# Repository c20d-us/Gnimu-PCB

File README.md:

<p>
  
  <picture>
    <source media="(prefers-color-scheme: dark)" srcset="https://raw.githubusercontent.com/c20d-us/Gnimu-branding/main/wordmark/gnimu-wordmark-transparent-white.svg">
    
  </picture>
</p>

# Gnimu PCBs

Circuit boards for [Gnimu](https://github.com/c20d-us/Gnimu), a GNSS+IMU motorsports telemetry device that streams live position, speed, and motion data over BLE.

This repository holds the hardware only: KiCad projects, the shared symbol and footprint library, and fabrication outputs. The firmware, the bill of materials, and the step-by-step build guides live in the [Gnimu](https://github.com/c20d-us/Gnimu) repository.

<table>
  <tr>
    <td align="center" valign="top" width="50%">
      <br>
      <sub>The bare carrier (revision v1.0), front and back.</sub>
    </td>
    <td align="center" valign="top" width="50%">
      <br>
      <sub>Loaded: the XIAO, the XL63070 regulator, the two resistors, and leads.</sub>
    </td>
  </tr>
</table>

---

## Boards

| Board | Revision | MCU | Status |
|---|---|---|---|
| [**Gnimu carrier (XIAO)**](boards/gnimu/) | [v1.1](boards/gnimu/gnimu-carrier-xiao-v1.1/) | Seeed XIAO nRF52840 Sense | Current design. Gerbers not yet added. |
| | [v1.0](boards/gnimu/gnimu-carrier-xiao-v1.0/) | Seeed XIAO nRF52840 Sense | Fabricated and built. Gerbers included. |
| [**Gnimu-CAN OBD-II helper**](boards/gnimu-can/gnimu-can-obd-helper-v1.1/) | [v1.1](boards/gnimu-can/gnimu-can-obd-helper-v1.1/) | None | Layout complete. Not yet ordered. Swaps the 12V socket's pins to match stock leads. |
| | [v1.0](boards/gnimu-can/gnimu-can-obd-helper-v1.0/) | None | Ordered 2026-10-24. 12V socket pins reversed; see its README. |
| [**Gnimu-CAN carrier (XIAO)**](boards/gnimu-can/) | [LiPo v1.0](boards/gnimu-can/gnimu-can-carrier-xiao-lipo-v1.0/) | Seeed XIAO ESP32C6 | Layout complete. Not yet ordered. |
| | [12V v1.0](boards/gnimu-can/gnimu-can-carrier-xiao-12v-v1.0/) | Seeed XIAO ESP32C6 | Layout complete. Not yet ordered. |

Every board is two-layer and built for hand assembly. The carriers are through-hole only, built around off-the-shelf modules that solder straight onto them; the OBD-II helper adds one SOT-23 part.

---

## Repo layout

```
boards/
  gnimu/                 The GNSS+IMU carrier, one folder per revision
  gnimu-can/             Gnimu-CAN boards: the OBD-II helper and the LiPo and 12V CAN carriers (work in progress)
libraries/               Shared KiCad symbols (Gnimu.kicad_sym) and footprints (Gnimu.pretty)
silkscreen-logos/        The Gnimu logo as SVG, sized for silkscreen
images/                  Board photos
```

Each revision folder is a self-contained KiCad project. Where a revision has been sent out for fabrication, its `fabrication/` folder holds the gerbers as they were ordered.

---

## Opening the projects

The projects are KiCad 10 files. Clone the repository and open any `.kicad_pro`.

The custom parts come from [`libraries/`](libraries/), which each project finds through its own `sym-lib-table` and `fp-lib-table` using a path relative to the project. There is nothing to install or configure, provided the folder layout is kept as it is.

---

## License & Terms

This source describes Open Hardware and is licensed under [CERN-OHL-S v2][CERN-OHL-S_v2]. You may redistribute and modify this source and make products using it under the terms of this license. Please see the text of CERN-OHL-S v2 for all applicable conditions that apply.

This source is distributed WITHOUT ANY EXPRESS OR IMPLIED WARRANTY, INCLUDING OF MERCHANTABILITY, SATISFACTORY QUALITY AND FITNESS FOR A PARTICULAR PURPOSE.

The Gnimu firmware is a separate work under its own license; see the [Gnimu](https://github.com/c20d-us/Gnimu) repository.

The Gnimu name and logo, including the silkscreen logo on the boards, are not covered by this license. You may leave the logo on a board made from an unmodified design. If you modify a design, remove the logo. See the [Gnimu branding usage policy](https://github.com/c20d-us/Gnimu-branding/blob/main/LICENSE.md).

[CERN-OHL-S_v2]: https://ohwr.org/cern_ohl_s_v2.txt

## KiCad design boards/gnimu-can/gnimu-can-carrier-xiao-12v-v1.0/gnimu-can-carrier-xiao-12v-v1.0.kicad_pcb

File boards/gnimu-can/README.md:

# Gnimu-CAN

Boards for Gnimu-CAN, a work-in-progress telemetry reader that takes data from a car's CAN bus through its OBD-II port, or directly from the CAN bus's CAN-H/CAN-L. The device uses a Seeed XIAO ESP32C6 MCU with an Adafruit CAN Pal transceiver. It runs either from its own LiPo battery or from the car's 12V supply, depending on which carrier it's built on.

> [!NOTE]
> **Work in progress.** Anything here may change. No boards other than the OBD-II Helper board have been sent to a fab.

## Boards

| Board | Folder | Status |
|---|---|---|
| [**OBD-II helper v1.0**](gnimu-can-obd-helper-v1.0/) | `gnimu-can-obd-helper-v1.0/` | Ordered from OSH Park 2026-10-24. J2's +12V and GND pins are reversed relative to stock red/black leads; see its README. |
| [**OBD-II helper v1.1**](gnimu-can-obd-helper-v1.1/) | `gnimu-can-obd-helper-v1.1/` | Layout complete. Not yet ordered. J2 swapped to pin 1 GND, pin 2 +12V; ground pour on both layers. |
| **CAN carrier (XIAO), LiPo v1.0** | [`gnimu-can-carrier-xiao-lipo-v1.0/`](gnimu-can-carrier-xiao-lipo-v1.0/) | Layout complete and passing DRC. Not yet ordered. |
| **CAN carrier (XIAO), 12V v1.0** | [`gnimu-can-carrier-xiao-12v-v1.0/`](gnimu-can-carrier-xiao-12v-v1.0/) | Layout complete and passing DRC. Not yet ordered. |

### OBD-II helper

A small board that fits over the exposed pins on the back of a straight-pin OBD-II plug and breaks out CAN_H, CAN_L and GND to a 3-pin JST PH socket, and 12V and GND to an optional 2-pin one, with a TVS diode on the CAN lines. See [its README](gnimu-can-obd-helper-v1.0/).

### CAN carriers (XIAO)

Two carriers in the same style as the [Gnimu carrier](../gnimu/): off-the-shelf modules on a simple two-layer, through-hole board. They share the same CAN section and differ only in how they're powered:

- **LiPo:** the XIAO runs from a 3.7V LiPo through its battery pads. Only CAN_H, CAN_L and GND come from the car.
- **12V:** the XIAO runs from the car's 12V, through a fuse, a TVS diode and a 5V buck regulator. It takes CAN_H, CAN_L, GND and +12V from the helper's two sockets.

All the off-board connections are plated holes for soldering leads, typically JST PH pigtails that plug into the helper. Unplated strain-relief holes (SR1, SR2…) sit beside the pads. The four corner holes are for M2.5 standoffs.

#### Shared CAN section

| Ref | Part | Role |
|---|---|---|
| **U1** | Seeed XIAO ESP32C6 | MCU, by its 14 edge pins. |
| **U2** | Adafruit CAN Pal | CAN transceiver breakout, powered from the XIAO's 3V3. |
| **R1** | 10kΩ | Pulls `CAN_SILENT` up, so the transceiver stays in listen-only mode until the firmware drives it low. |
| **J1** | 3 wire pads | CAN from the OBD-II helper: 1 CAN_H · 2 GND · 3 CAN_L, the same order as the helper's J3. |

| XIAO pin | Net | Goes to |
|---|---|---|
| D0/A0 | `VBAT_SENSE` (LiPo) or `V12_SENSE` (12V) | Supply voltage divider tap |
| D8 | `CAN_SILENT` | CAN Pal S (high = listen-only) |
| D9 | `CAN_TX` | CAN Pal TX |
| D10 | `CAN_RX` | CAN Pal RX |

The CAN Pal's own termination switch is left off: the car's bus is already terminated.

#### LiPo carrier

48 × 44 mm. All parts are through-hole.

| Ref | Part | Role |
|---|---|---|
| **R2, R3** | 100kΩ + 100kΩ | Battery voltage divider to D0/A0 (÷2). |
| **C1** | 100nF | Steadies the divider tap for the ADC. |
| **J2** | 2 wire pads | Power switch. |
| **J3** | 2 wire pads | LiPo battery. |
| **J4** | 2 wire pads | Leads to the XIAO's battery pads. |

The battery runs through the switch to `VSYS`, which feeds the XIAO's battery pads and the divider, so the switch turns off everything, divider included.

The XIAO's built-in charger works through those same battery pads, so the LiPo charges over USB only while the switch is on. With the switch off, the battery is fully disconnected and nothing drains it.

#### 12V carrier

56 × 44 mm. All parts are through-hole.

| Ref | Part | Role |
|---|---|---|
| **J2** | 2 wire pads | 12V in from the helper's J2. |
| **F1** | Bourns MF-R050 | Resettable PTC fuse: 0.5A hold, 1A trip, 60V. |
| **D1** | P6KE18A | Unidirectional TVS diode: 15.3V standoff, about 25V clamp. Cathode to the fused 12V. |
| **D2** | 1N5819 | Series Schottky diode after D1, for reverse-polarity protection. |
| **J3** | 2 wire pads | Power switch: **Common** (protected 12V) and **On** (switched 12V). |
| **C1** | 47µF / 35V electrolytic (Rubycon 35YXJ47M5X11) | Input bulk capacitor, close to U3's VIN as Pololu recommends. |
| **U3** | Pololu D24V7F5 | 5V 600mA step-down regulator, 5.1–36V in. |
| **D3** | 1N5819 | Schottky diode from U3's output to the XIAO's 5V (VBUS) pin. |
| **R2, R3** | 100kΩ + 10kΩ | Divider from the switched 12V to D0/A0 (÷11). |
| **C2** | 100nF | Steadies the divider tap for the ADC. |

The power path is:

```
J2 +12V → F1 → D1 (to GND) → D2 → J3 switch → C1 → U3 → D3 → XIAO 5V pin
```

- **Reverse polarity.** The D24V7F5 has no reverse-voltage protection of its own. If 12V is connected backwards, D1 conducts forward and F1 trips, while D2 blocks the negative voltage so the regulator, C1 and the divider never see it. F1 resets once the fault is removed.
- **Overvoltage.** If the input rises well above about 17V, D1 breaks down and clamps it, and a sustained overvoltage trips F1. D1 also clamps negative spikes before they reach D2.
- **D3** keeps the XIAO's USB 5V from feeding back into the regulator when a USB cable is plugged in. Seeed recommends a diode like this whenever the 5V pin is powered externally.
- **The switch** sits after the fuse and TVS, so it turns off the regulator, the XIAO and the divider together. To build without a switch (like if you get +12V from a switched source rather than the OBD-II port), bridge J3 with a wire link, or fit a 2-pin header and a jumper.
- **The divider** gives 1.35V at 14.8V and 3.27V at 36V, so the ADC covers the regulator's whole input range. Multiply the reading at D0 by 11, then add about 0.35V for D2's drop, to get the supply voltage.
- **Antenna.** The XIAO's antenna is at the end opposite its USB port. A keep-out zone on both copper layers keeps tracks and the ground pour away from it.

The symbols, footprints and 3D models for all the boards are in the shared [`libraries/`](../../libraries/) folder.

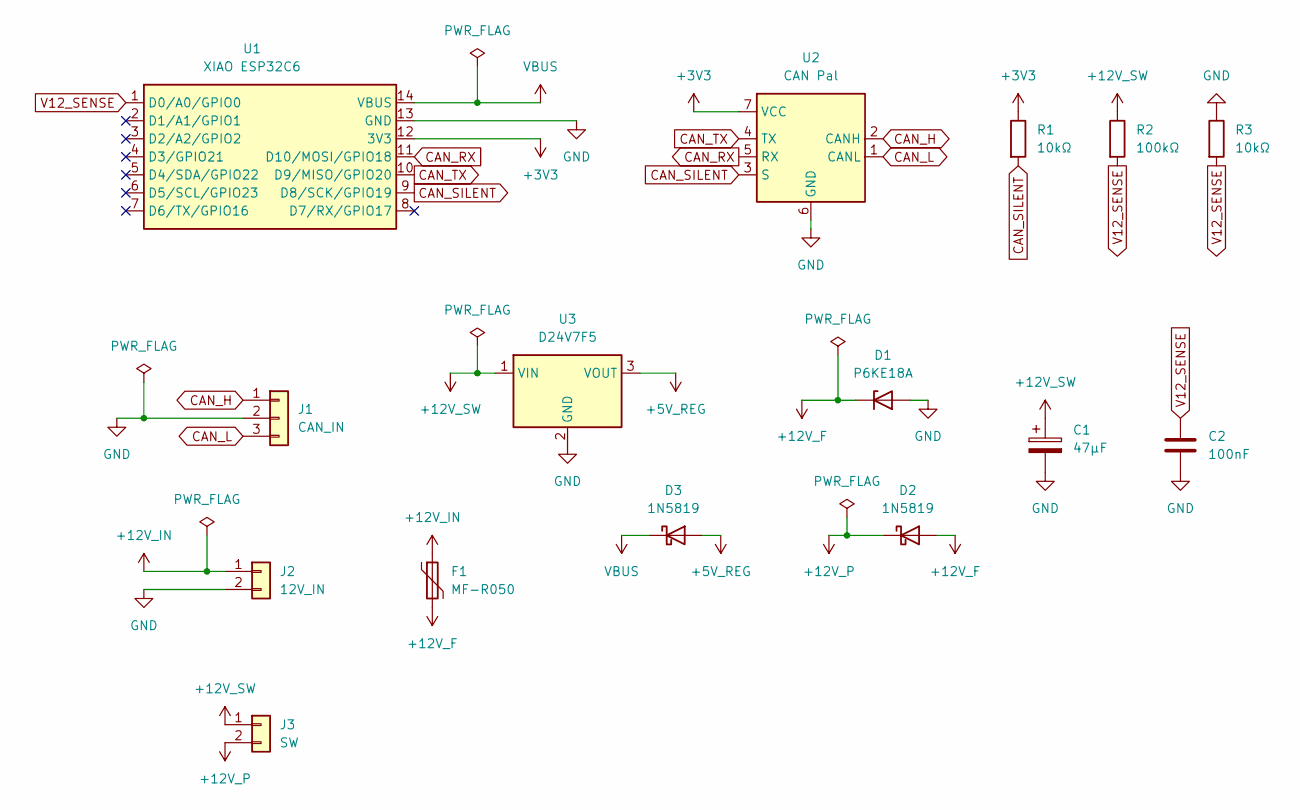
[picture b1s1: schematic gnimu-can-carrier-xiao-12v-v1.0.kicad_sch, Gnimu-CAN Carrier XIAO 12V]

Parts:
C1: 47µF; CP_Radial_D5.0mm_P2.00mm
C2: 100nF; C_Disc_D3.0mm_W2.0mm_P2.50mm
D1: P6KE18A; D_DO-15_P10.16mm_Horizontal
D2, D3: 1N5819; D_DO-41_SOD81_P10.16mm_Horizontal
F1: MF-R050; C_Disc_D7.5mm_W5.0mm_P5.00mm
J1: CAN_IN; Holes_1x03_P2.54mm
J2: 12V_IN; Holes_1x02_P2.54mm
J3: SW; Holes_1x02_P2.54mm
R1, R3: 10kΩ; R_Axial_DIN0207_L6.3mm_D2.5mm_P10.16mm_Horizontal
R2: 100kΩ; R_Axial_DIN0207_L6.3mm_D2.5mm_P10.16mm_Horizontal
U1: XIAO ESP32C6; XIAO_ESP32C6_THT
U2: CAN Pal; Adafruit_CAN_Pal_THT
U3: D24V7F5; Pololu_D24V7Fx_THT

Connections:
+3V3: R1.1, U1.12 (3V3), U2.7 (VCC)
+5V_REG: D3.2 (A), U3.3 (VOUT)
+12V_F: D1.1 (K), D2.2 (A), F1.2
+12V_IN: F1.1, J2.1
+12V_P: D2.1 (K), J3.2
+12V_SW: C1.1, J3.1, R2.1, U3.1 (VIN)
CAN_H: J1.1, U2.2 (CANH)
CAN_L: J1.3, U2.1 (CANL)
CAN_RX: U1.11 (D10/MOSI/GPIO18), U2.5 (RX)
CAN_SILENT: R1.2, U1.9 (D8/SCK/GPIO19), U2.3 (S)
CAN_TX: U1.10 (D9/MISO/GPIO20), U2.4 (TX)
GND: C1.2, C2.2, D1.2 (A), J1.2, J2.2, R3.1, U1.13 (GND), U2.6 (GND), U3.2 (GND)
V12_SENSE: C2.1, R2.2, R3.2, U1.1 (D0/A0/GPIO0)
VBUS: D3.1 (K), U1.14 (VBUS)

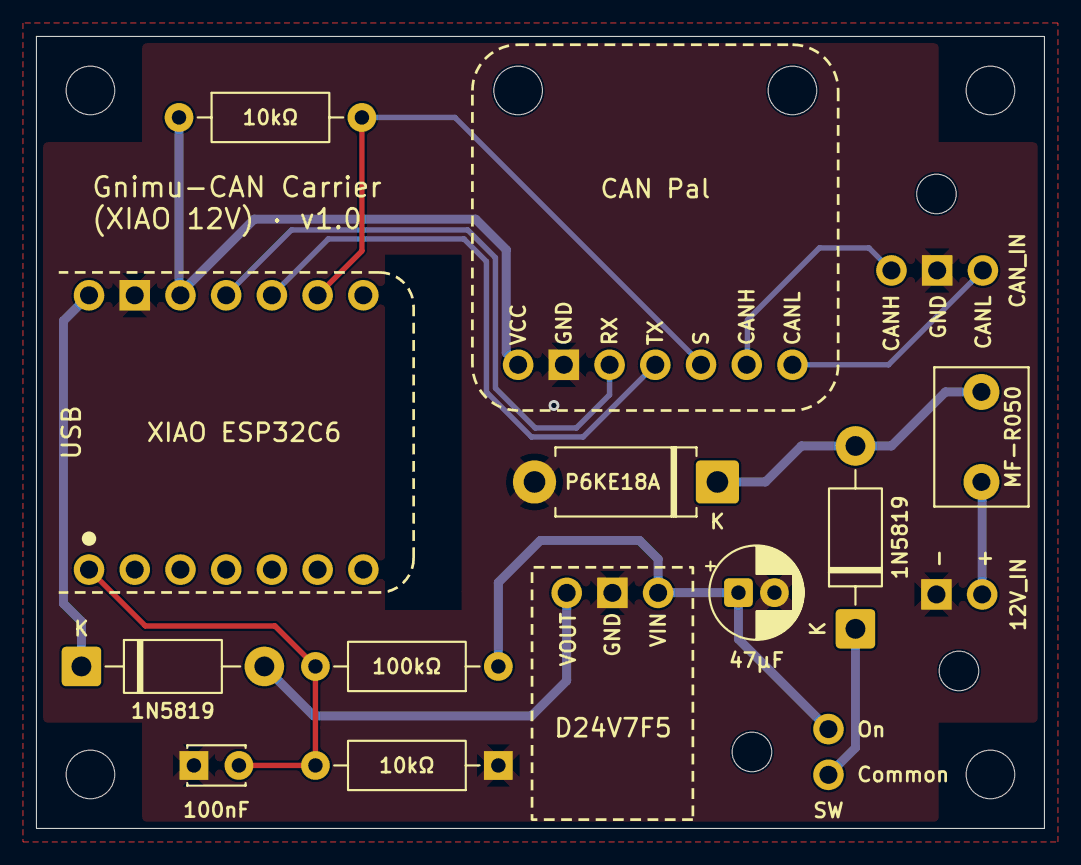
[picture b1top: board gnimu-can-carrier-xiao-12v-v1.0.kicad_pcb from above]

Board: 2 copper layers, 56.0 x 44.0 mm, 22 parts (0 on the bottom side), 14 nets.

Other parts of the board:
M1: M1; MountingHole_2.7mm_M2.5
M2: M2; MountingHole_2.7mm_M2.5
M3: M3; MountingHole_2.7mm_M2.5
M4: M4; MountingHole_2.7mm_M2.5
SR1, SR2, SR3: MountingHole_2.2mm_M2

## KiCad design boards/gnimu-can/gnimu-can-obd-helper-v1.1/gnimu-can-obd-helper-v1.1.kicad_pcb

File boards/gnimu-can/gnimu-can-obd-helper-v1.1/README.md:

# Gnimu-CAN OBD-II helper (v1.1)

A small board that fits over the exposed pins on the back of a straight-pin J1962 (OBD-II) plug and breaks the car's CAN bus and 12V supply out to JST PH sockets. It saves soldering wires directly to the plug's pins.

It is part of the Gnimu-CAN telemetry reader. The CAN socket feeds either [CAN carrier](../); the 12V socket is needed only for the 12V carrier and can be left unpopulated for the LiPo one.

> [!NOTE]
> **Not yet ordered.** v1.1 has passed ERC and DRC but hasn't been fabricated.

## Changes from v1.0

- **J2's pins are swapped:** pin 1 is now GND and pin 2 is +12V. Pre-made red/black JST PH leads then plug in with red on +12V and black on GND, with no re-pinning. See the warning in the [v1.0 README](../gnimu-can-obd-helper-v1.0/).
- **Square pads mark ground.** Every GND pad is square and only GND pads are square: J2 pin 1, J3 pin 2, and the OBD plug's ground slots (pins 4 and 5). J3's pin 1 is a plain oval pad; the socket's keyed shroud and silkscreen outline mark its orientation.
- **45° thermal spokes** on the ground pads, which fit more spokes between the closely spaced pins.
- **Ground pour on both layers** instead of the back only.
- **The +12V trace is 0.5 mm** (it was 0.8 mm) and is shorter, running from J2 pin 2 to OBD pin 16.

---

## The board

| | |
|---|---|
| Size | 37.6 × 17.1 mm, with about 0.5 mm corner radii |
| Layers | 2, 1.6 mm |
| Faces | **Front (F.Cu)** faces outward and carries the sockets and the TVS diode. **Back (B.Cu)** sits against the plug's flange. Both carry a ground pour. |
| Fits | The flange of a straight-pin J1962 plug, 37.6 × 17.2 mm. The board is centred on the pin array, which is centred on the flange. |

The outline is 0.05 mm narrower than the flange. The back-side silkscreen (copyright, licence and repo) is hidden against the flange when the board is installed.

### Sockets

| Ref | Socket | Pins | Use |
|---|---|---|---|
| **J3** | JST PH, 3-pin (B3B-PH-K-S) | 1 CAN_H · 2 GND · 3 CAN_L | CAN bus to the Gnimu-CAN device. |
| **J2** | JST PH, 2-pin (B2B-PH-K-S) | 1 GND · 2 +12V | Optional 12V feed. Leave it unpopulated if it isn't needed. |

The silkscreen labels them `CAN_H | GND | CAN_L` and `GND | +12V`.

Check your leads before plugging them in. The red/black PH leads bought for this project have black on pin 1 and red on pin 2, which matches v1.1's J2. Leads from other sellers may differ.

### Pin map

| Net | OBD-II pin | Connections on the board |
|---|---|---|
| CAN_H | 6 | J3 pin 1, D1 pin 1 |
| CAN_L | 14 | J3 pin 3, D1 pin 2 |
| GND | 4 (chassis) and 5 (signal) | J3 pin 2, J2 pin 1, D1 pin 3, ground pour on both layers |
| +12V | 16 | J2 pin 2 |
| Not connected | 1–3, 7–13, 15 | |

Pin 1 is upper left and pin 16 lower right, viewed from the flange side. The pin numbers 1, 8, 9 and 16 are printed on the front.

### Protection

**D1** is an onsemi NUP2105L dual-line CAN bus TVS diode (SOT-23) on CAN_H and CAN_L, clamping to ground. It has a 24V minimum working voltage and clamps at about 33V at 5A.

There is **no fuse** and **no CAN termination** on the board:

- If you use the 12V socket, fuse the link where it lands. The 12V carrier does this with a PTC fuse (F1) right at its input; anything else should have its own fuse.
- The car's bus is already terminated. Don't add 120Ω termination across CAN_H and CAN_L, and leave a transceiver module's own termination switched off (the Adafruit CAN Pal has one).

---

## Parts

| Ref | Part | Notes |
|---|---|---|
| J1 | Straight-pin J1962 OBD-II plug | The board solders onto its pins. Not part of the board's BOM. |
| J2 | JST B2B-PH-K-S | 2-pin PH vertical header, 2.0 mm pitch. Optional. Mates with a PHR-2 housing. |
| J3 | JST B3B-PH-K-S | 3-pin PH vertical header, 2.0 mm pitch. Mates with a PHR-3 housing. |
| D1 | onsemi NUP2105L | SOT-23. The only surface-mount part. |

---

## Design notes

### The J1962 footprint

The plug footprint is `Gnimu:OBD2_J1962_Plug_Straight_16P` in the shared [library](../../../libraries/), with the symbol `OBD2_J1962_Plug_16P`.

- 16 plated slots: 2.54 × 1.83 mm pads with 2.03 × 0.97 mm slot drills, for 1.8 × 0.75 mm pins. On this board the two ground slots (pins 4 and 5) have square pads; the rest are oval.
- 4.0 mm pitch along each row of eight, and 8.6 mm pitch between the two rows.
- The flange outline (37.6 × 17.2 mm) and the trench behind the pins (31.8 × 5.75 mm, 3.7 mm deep) are drawn on `Dwgs.User` for reference. They are kept off the courtyard layer so they don't raise courtyard errors against the other parts.

The square ground pads and 45° spokes are set on this board's copies of the footprints, not in the libraries, so DRC reports that J1, J2 and J3 differ from their library versions. That's expected. **Update Footprint from Library** would undo them.

### The plug

- The trench behind the pins is where the PH headers' through-hole tails end up.
- The plug's pins stand 4 mm proud of its back face, except the two ground pins (4 and 5), which stand only 2.5 mm proud. Through a 1.6 mm board that leaves about 2.4 mm for most pins to solder to, but only about 0.9 mm for pins 4 and 5.

### Layout

- The CAN traces are 0.3 mm wide and close in length (about 23.1 and 22.4 mm), all on the front.
- The +12V trace is 0.5 mm wide, about 5 mm long, and runs on the back. The 12V carrier's fuse trips at about 1A, well within what it carries.
- A single GND zone covers both layers, with 0.5 mm thermal gaps and 0.5 mm spokes. The two pours are joined through the ground pins and slots.

---

## Fabrication

The KiCad project is the source. v1.1 hasn't been ordered yet; gerbers will go in a `fabrication/` folder when it is.

v1.0 was ordered from OSH Park's standard 2-layer service by uploading the `.kicad_pcb` file directly, and the same works for v1.1. OSH Park detects and supports the plated slots.

> [!IMPORTANT]
> OSH Park does not refill KiCad zones. If you upload the `.kicad_pcb`, refill the zones (press **B** in the PCB editor) and save first, or the ground pour may be stale.

Other board houses should work from the gerbers, provided they support plated slots (the narrowest here is 0.97 mm).

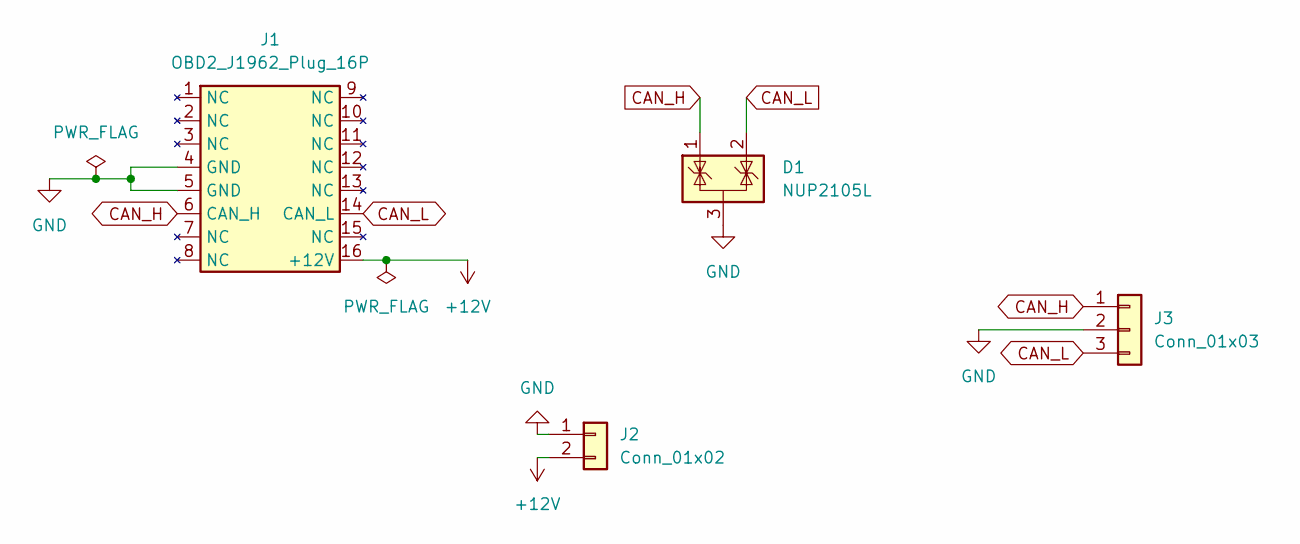
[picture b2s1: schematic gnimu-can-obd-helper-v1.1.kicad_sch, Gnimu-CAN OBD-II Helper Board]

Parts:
D1: NUP2105L; SOT-23
J1: OBD2_J1962_Plug_16P; OBD2_J1962_Plug_Straight_16P
J2: Conn_01x02; JST_PH_B2B-PH-K_1x02_P2.00mm_Vertical
J3: Conn_01x03; JST_PH_B3B-PH-K_1x03_P2.00mm_Vertical

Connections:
+12V: J1.16 (+12V), J2.2
CAN_H: D1.1 (K), J1.6 (CAN_H), J3.1
CAN_L: D1.2 (K), J1.14 (CAN_L), J3.3
GND: D1.3 (A), J1.4 (GND), J1.5 (GND), J2.1, J3.2

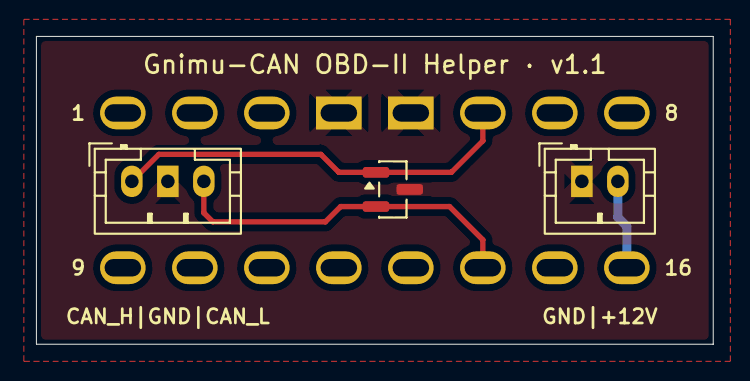
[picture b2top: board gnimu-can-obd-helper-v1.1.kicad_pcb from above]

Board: 2 copper layers, 37.6 x 17.1 mm, 4 parts (0 on the bottom side), 4 nets.

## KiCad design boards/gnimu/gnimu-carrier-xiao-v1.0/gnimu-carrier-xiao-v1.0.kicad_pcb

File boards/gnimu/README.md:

# Gnimu carrier (XIAO)

A small through-hole carrier for the portable, battery-powered [Gnimu](https://github.com/c20d-us/Gnimu) build. A Seeed XIAO nRF52840 Sense and an XL63070 buck-boost module solder onto it, and labelled pads take the leads for everything else. It replaces the point-to-point wiring of a hand-wired build; the connections and the firmware are the same either way.

For the parts list, assembly steps, and usage, follow the [XIAO nRF52840 build guide](https://github.com/c20d-us/Gnimu/blob/main/docs/build-nrf52840.md) in the Gnimu repository.

---

## Revisions

| Revision | Date | Folder | Fabrication outputs |
|---|---|---|---|
| **v1.1** | 2026-10-10 | [`gnimu-carrier-xiao-v1.1/`](gnimu-carrier-xiao-v1.1/) | Not yet added |
| **v1.0** | 2026-09-27 | [`gnimu-carrier-xiao-v1.0/`](gnimu-carrier-xiao-v1.0/) | [`fabrication/`](gnimu-carrier-xiao-v1.0/fabrication/), gerbers as ordered from JLCPCB |

**v1.1** differs from v1.0 only in its larger mounting holes (2.7mm for M2.5, up from 2.2mm for M2) and a printed reminder of the regulator's settings, `PS open · 3V3`. The two are wired identically.

---

## The board

- 74.8 × 44.8 mm, two copper layers, through-hole only.
- Six mounting holes, at the corners and the middle of each long edge.
- A pair of tie-down holes beside each of the GNSS, BATT, Switch and XIAO BATT pads, for strain-relieving the leads.
- The Gnimu logo and the revision on both sides.

### Soldered on

| Silkscreen | Part |
|---|---|
| **XIAO nRF52840 Sense** | The XIAO, by its 14 edge pins, with its USB connector at the board edge marked **USB**. |
| **XL63070** | The XL63070 (TPS63070) buck-boost module, the 3.3V version, with its PS solder jumper left open as supplied. |
| **510kΩ** (two positions) | The switch-sense voltage divider. |

### Wire pads

All pads are on a 2.54mm pitch.

| Silkscreen | Pads | Connects to |
|---|---|---|
| **GNSS** | G · V · TX · RX | The GNSS module: ground, 3.3V power, and the module's own TX and RX pins. |
| **BATT** | + · − | The LiPo. |
| **Switch** | ON · COMMON · OFF | The slide switch: its common terminal to COMMON, its two throws to ON and OFF. |
| **XIAO BATT** | + · − | The battery pads on the underside of the XIAO. |
| **I2C** | GND · 3V3 · SDA · SCL | Spare. Not used by the firmware. |
| **GPIO** | GND · D10 · D9 · D8 · D2 · D3 | Spare. Not used by the firmware. |

The **TX** and **RX** pads are named for the GNSS module's pins: wire the module's TX to TX and its RX to RX. The crossover to the XIAO is done on the board.

### How it's wired

| XIAO pin | Goes to | Purpose |
|---|---|---|
| **D6** (Serial1 TX) | GNSS **RX** | UART |
| **D7** (Serial1 RX) | GNSS **TX** | UART |
| **D1** | Regulator **EN** | GNSS power control. The module's own pull-up keeps it on; the XIAO pulls it low to switch the GNSS off. |
| **D0 / A0** | Switch-sense divider tap | Reads about 2V with the switch off and about 0V with it on. |

```
        (+) ─ SW common
               │
  LiPo         ├─[ SW ON  ]──┬──────────────────────► XIAO BAT+
  3.7V         │             └──────────────────────► regulator VIN
               └─[ SW OFF ]──[ 510kΩ ]──┬───────────► XIAO D0/A0
                                        └─[ 510kΩ ]─► GND
        (–) ────────────────────────────────────────► XIAO BAT−, regulator GND, GNSS GND

  regulator VOUT (3.3V) ────────────────────────────► GNSS VCC
```

The regulator powers only the GNSS; the XIAO runs directly from the battery.

### Mounting orientation

The **IMU** axes printed beside the XIAO show how the board must sit in the car: the **X** arrow points to the front of the car and the **Y** arrow to its left, with the component side facing up. That puts the XIAO's USB connector toward the rear.

---

## Before connecting the GNSS

> [!WARNING]
> The regulator module can be supplied set to 9V, which will destroy the GNSS module. Confirm it is the 3.3V version and measure **VOUT** before the GNSS is connected. See the [build guide](https://github.com/c20d-us/Gnimu/blob/main/docs/build-nrf52840.md#check-the-regulator-before-connecting-the-gnss).

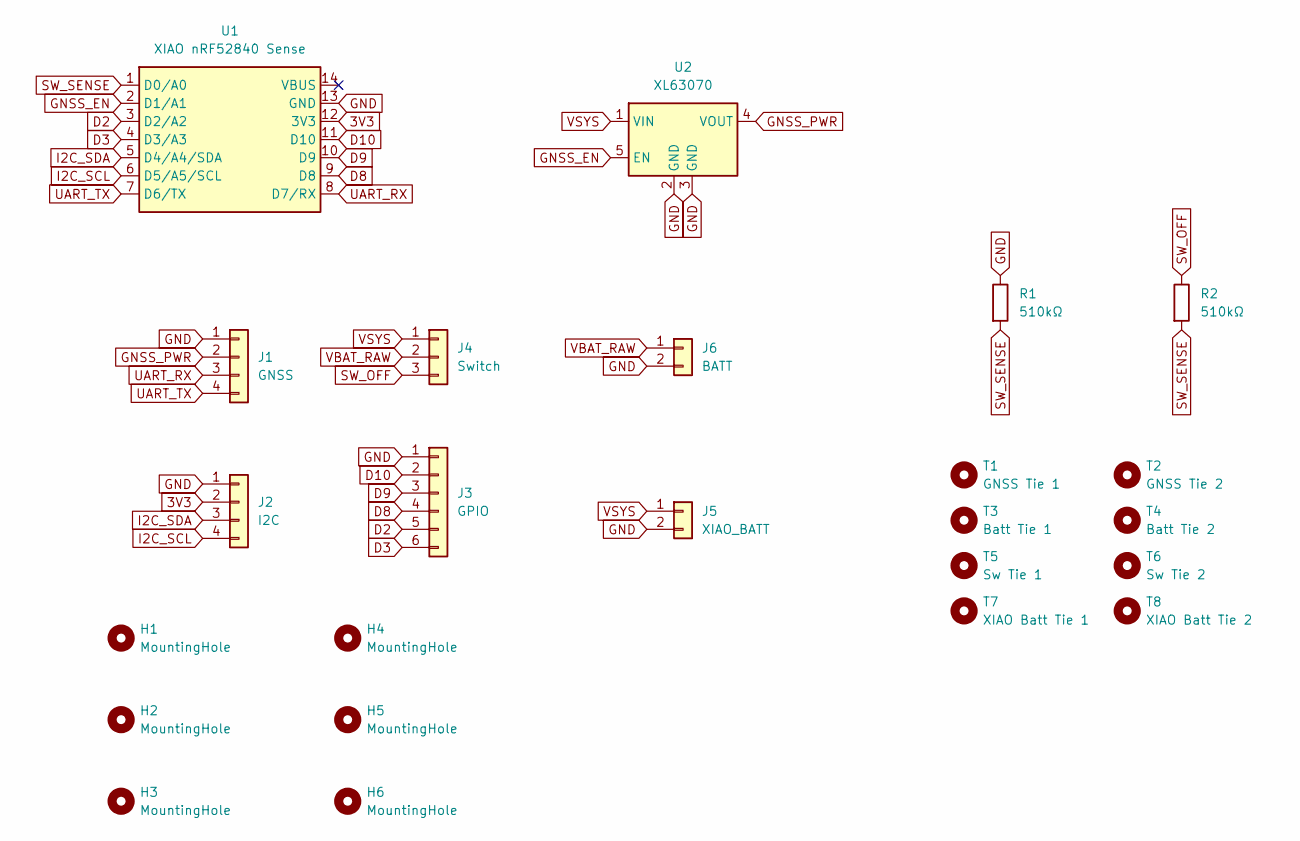
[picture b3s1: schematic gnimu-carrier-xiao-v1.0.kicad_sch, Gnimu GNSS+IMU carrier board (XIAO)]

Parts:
H1, H2, H3, H4, H5, H6: MountingHole; MountingHole_2.2mm_M2
J1: GNSS; Holes_1x04_P2.54mm
J2: I2C; Holes_1x04_P2.54mm
J3: GPIO; Holes_1x06_P2.54mm
J4: Switch; Holes_1x03_P2.54mm
J5: XIAO_BATT; Holes_1x02_P2.54mm
J6: BATT; Holes_1x02_P2.54mm
R1, R2: 510kΩ; R_Axial_DIN0207_L6.3mm_D2.5mm_P10.16mm_Horizontal
T1: GNSS Tie 1; MountingHole_2.2mm_M2
T2: GNSS Tie 2; MountingHole_2.2mm_M2
T3: Batt Tie 1; MountingHole_2.2mm_M2
T4: Batt Tie 2; MountingHole_2.2mm_M2
T5: Sw Tie 1; MountingHole_2.2mm_M2
T6: Sw Tie 2; MountingHole_2.2mm_M2
T7: XIAO Batt Tie 1; MountingHole_2.2mm_M2
T8: XIAO Batt Tie 2; MountingHole_2.2mm_M2
U1: XIAO nRF52840 Sense; XIAO_nRF52840_THT
U2: XL63070; XL63070_THT

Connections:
3V3: J2.2, U1.12 (3V3)
D2: J3.5, U1.3 (D2/A2)
D3: J3.6, U1.4 (D3/A3)
D8: J3.4, U1.9 (D8)
D9: J3.3, U1.10 (D9)
D10: J3.2, U1.11 (D10)
GND: J1.1, J2.1, J3.1, J5.2, J6.2, R1.1, U1.13 (GND), U2.2 (GND), U2.3 (GND)
GNSS_EN: U1.2 (D1/A1), U2.5 (EN)
GNSS_PWR: J1.2, U2.4 (VOUT)
I2C_SCL: J2.4, U1.6 (D5/A5/SCL)
I2C_SDA: J2.3, U1.5 (D4/A4/SDA)
SW_OFF: J4.3, R2.1
SW_SENSE: R1.2, R2.2, U1.1 (D0/A0)
UART_RX: J1.3, U1.8 (D7/RX)
UART_TX: J1.4, U1.7 (D6/TX)
VBAT_RAW: J4.2, J6.1
VSYS: J4.1, J5.1, U2.1 (VIN)

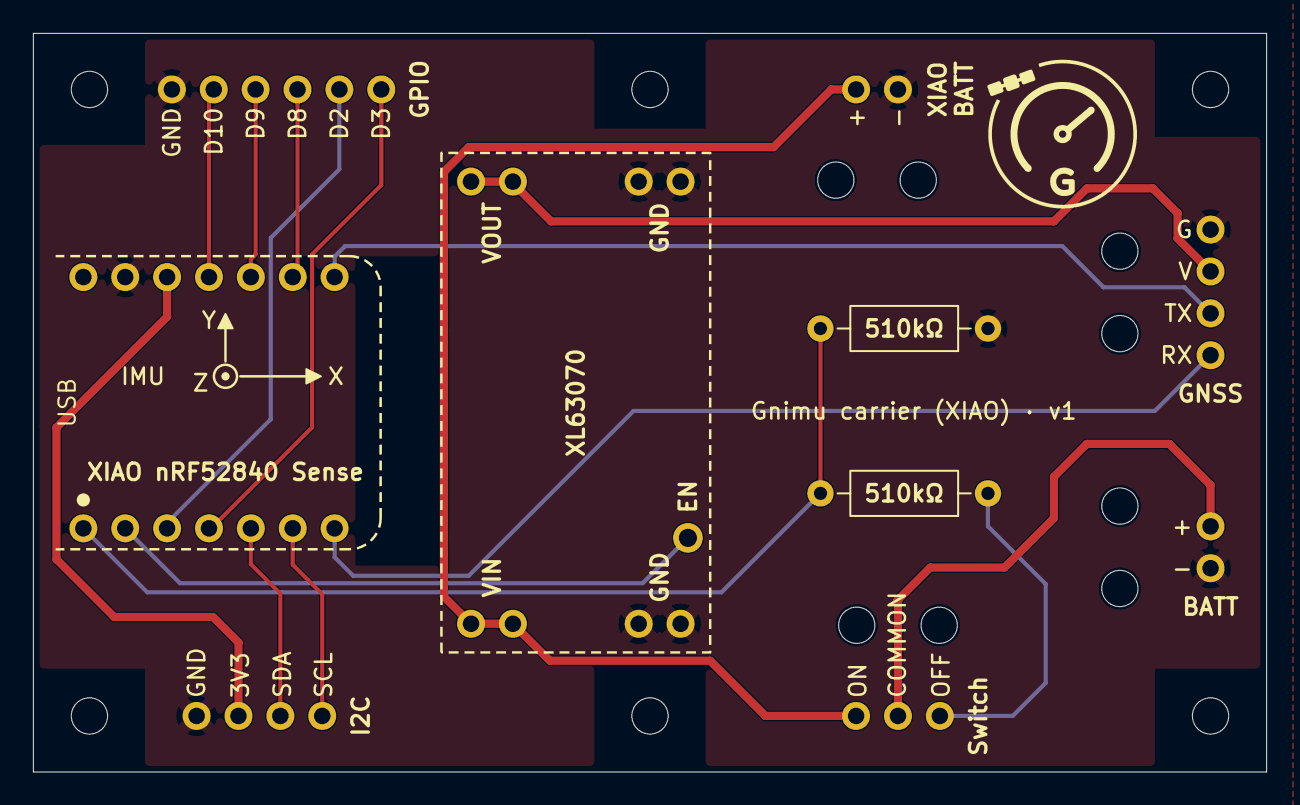
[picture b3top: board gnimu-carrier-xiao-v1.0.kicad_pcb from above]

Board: 2 copper layers, 74.8 x 44.8 mm, 24 parts (0 on the bottom side), 17 nets.

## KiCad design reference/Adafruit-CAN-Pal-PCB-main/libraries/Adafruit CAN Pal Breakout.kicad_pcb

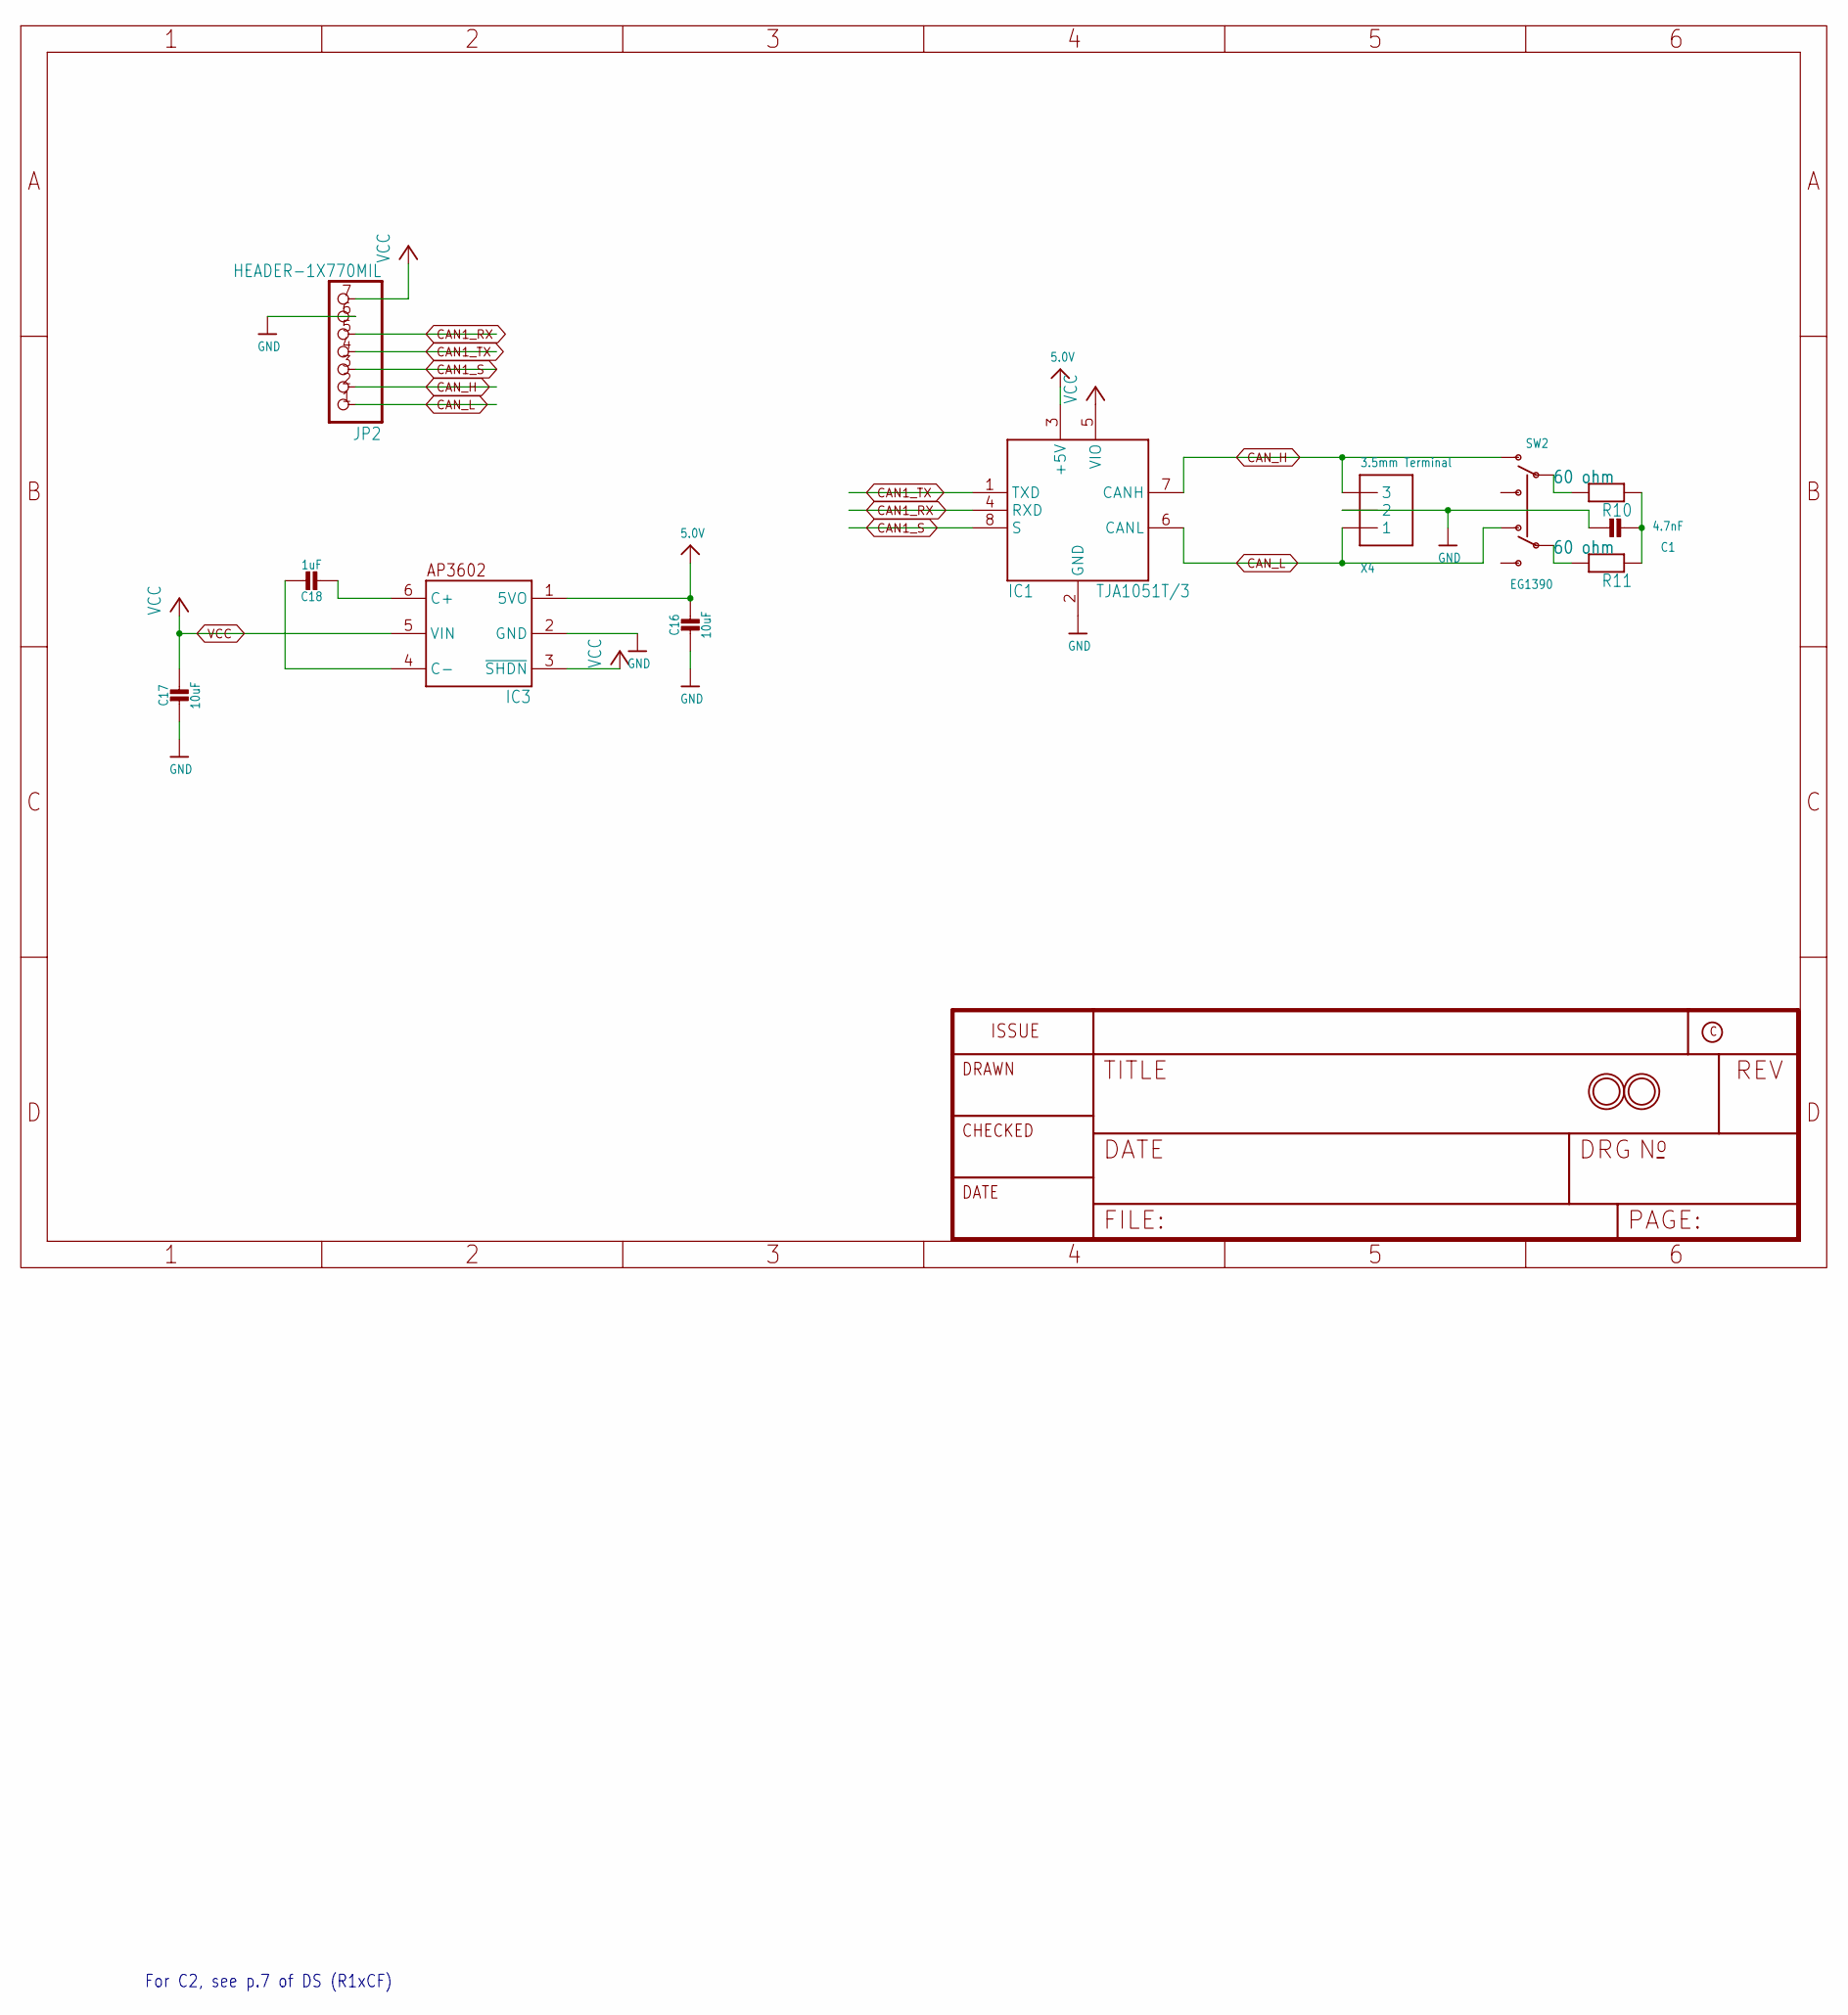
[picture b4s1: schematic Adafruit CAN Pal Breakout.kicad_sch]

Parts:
C1: 4.7nF; 0603-NO
C16, C17: 10uF; 0805-NO
C18: 1uF; 0805_10MGAP
IC1: TJA1051T/3; SOIC8_150MIL
IC3: AP3602; SOT23-6
JP2: HEADER-1X770MIL; 1X07_ROUND_70
R10, R11: 60 ohm; 0603-NO
SW2: EG1390; LCSC C2837066
U$2, U$3: MOUNTINGHOLE2.5; MOUNTINGHOLE_2.5_PLATED
X4: 3.5mm Terminal; TERMBLOCK_1X3-3.5MM

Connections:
5.0V: C16.1, IC1.3 (+5V), IC3.1 (5VO)
CAN1_RX: IC1.4 (RXD), JP2.5
CAN1_S: IC1.8 (S), JP2.3
CAN1_TX: IC1.1 (TXD), JP2.4
CAN_H: IC1.7 (CANH), JP2.2, SW2.O1, X4.3
CAN_L: IC1.6 (CANL), JP2.1, SW2.O2, X4.1
GND: C1.2, C16.2, C17.2, IC1.2 (GND), IC3.2 (GND), JP2.6, X4.2
unnamed: R10.2, SW2.P1
unnamed: R11.2, SW2.P2
unnamed: C18.2, IC3.6 (C+)
unnamed: C18.1, IC3.4 (C-)
unnamed: C1.1, R10.1, R11.1
VCC: C17.1, IC1.5 (VIO), IC3.3 (~SHDN), IC3.5 (VIN), JP2.7

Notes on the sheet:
For C2, see p.7 of DS (R1xCF)

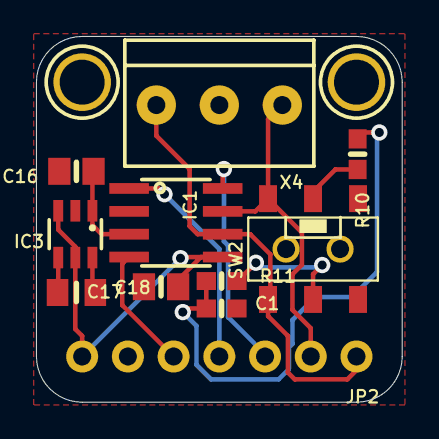
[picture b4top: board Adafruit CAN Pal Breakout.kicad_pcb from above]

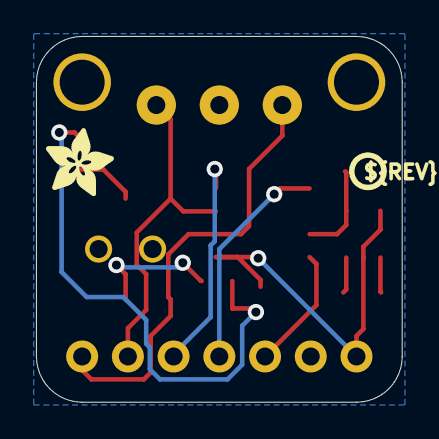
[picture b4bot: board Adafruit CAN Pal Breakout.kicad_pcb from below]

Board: 2 copper layers, 20.3 x 20.3 mm, 30 parts (5 on the bottom side), 13 nets.

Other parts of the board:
PLABEL0: PLABEL0
PLABEL1: PLABEL1
PLABEL2: PLABEL2
PLABEL3: PLABEL3
PLABEL4: PLABEL4
PLABEL5: PLABEL5
PLABEL6: PLABEL6
PLABEL7: PLABEL7
PLABEL8: PLABEL8
PLABEL9: PLABEL9
PLABEL10: PLABEL10
PLABEL11: PLABEL11
PLABEL12: PLABEL12
PLABEL13: PLABEL13
PLABEL14: PLABEL14
U$6: ADAFRUIT_3.5MM
U$7: PCBFEAT-REV-040

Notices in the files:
README.md:
License: CERN-OHL-S-2.0
boards/gnimu-can/gnimu-can-carrier-xiao-12v-v1.0/gnimu-can-carrier-xiao-12v-v1.0.kicad_pcb:
© 2026 C. Halstead
CERN-OHL-S-2.0
